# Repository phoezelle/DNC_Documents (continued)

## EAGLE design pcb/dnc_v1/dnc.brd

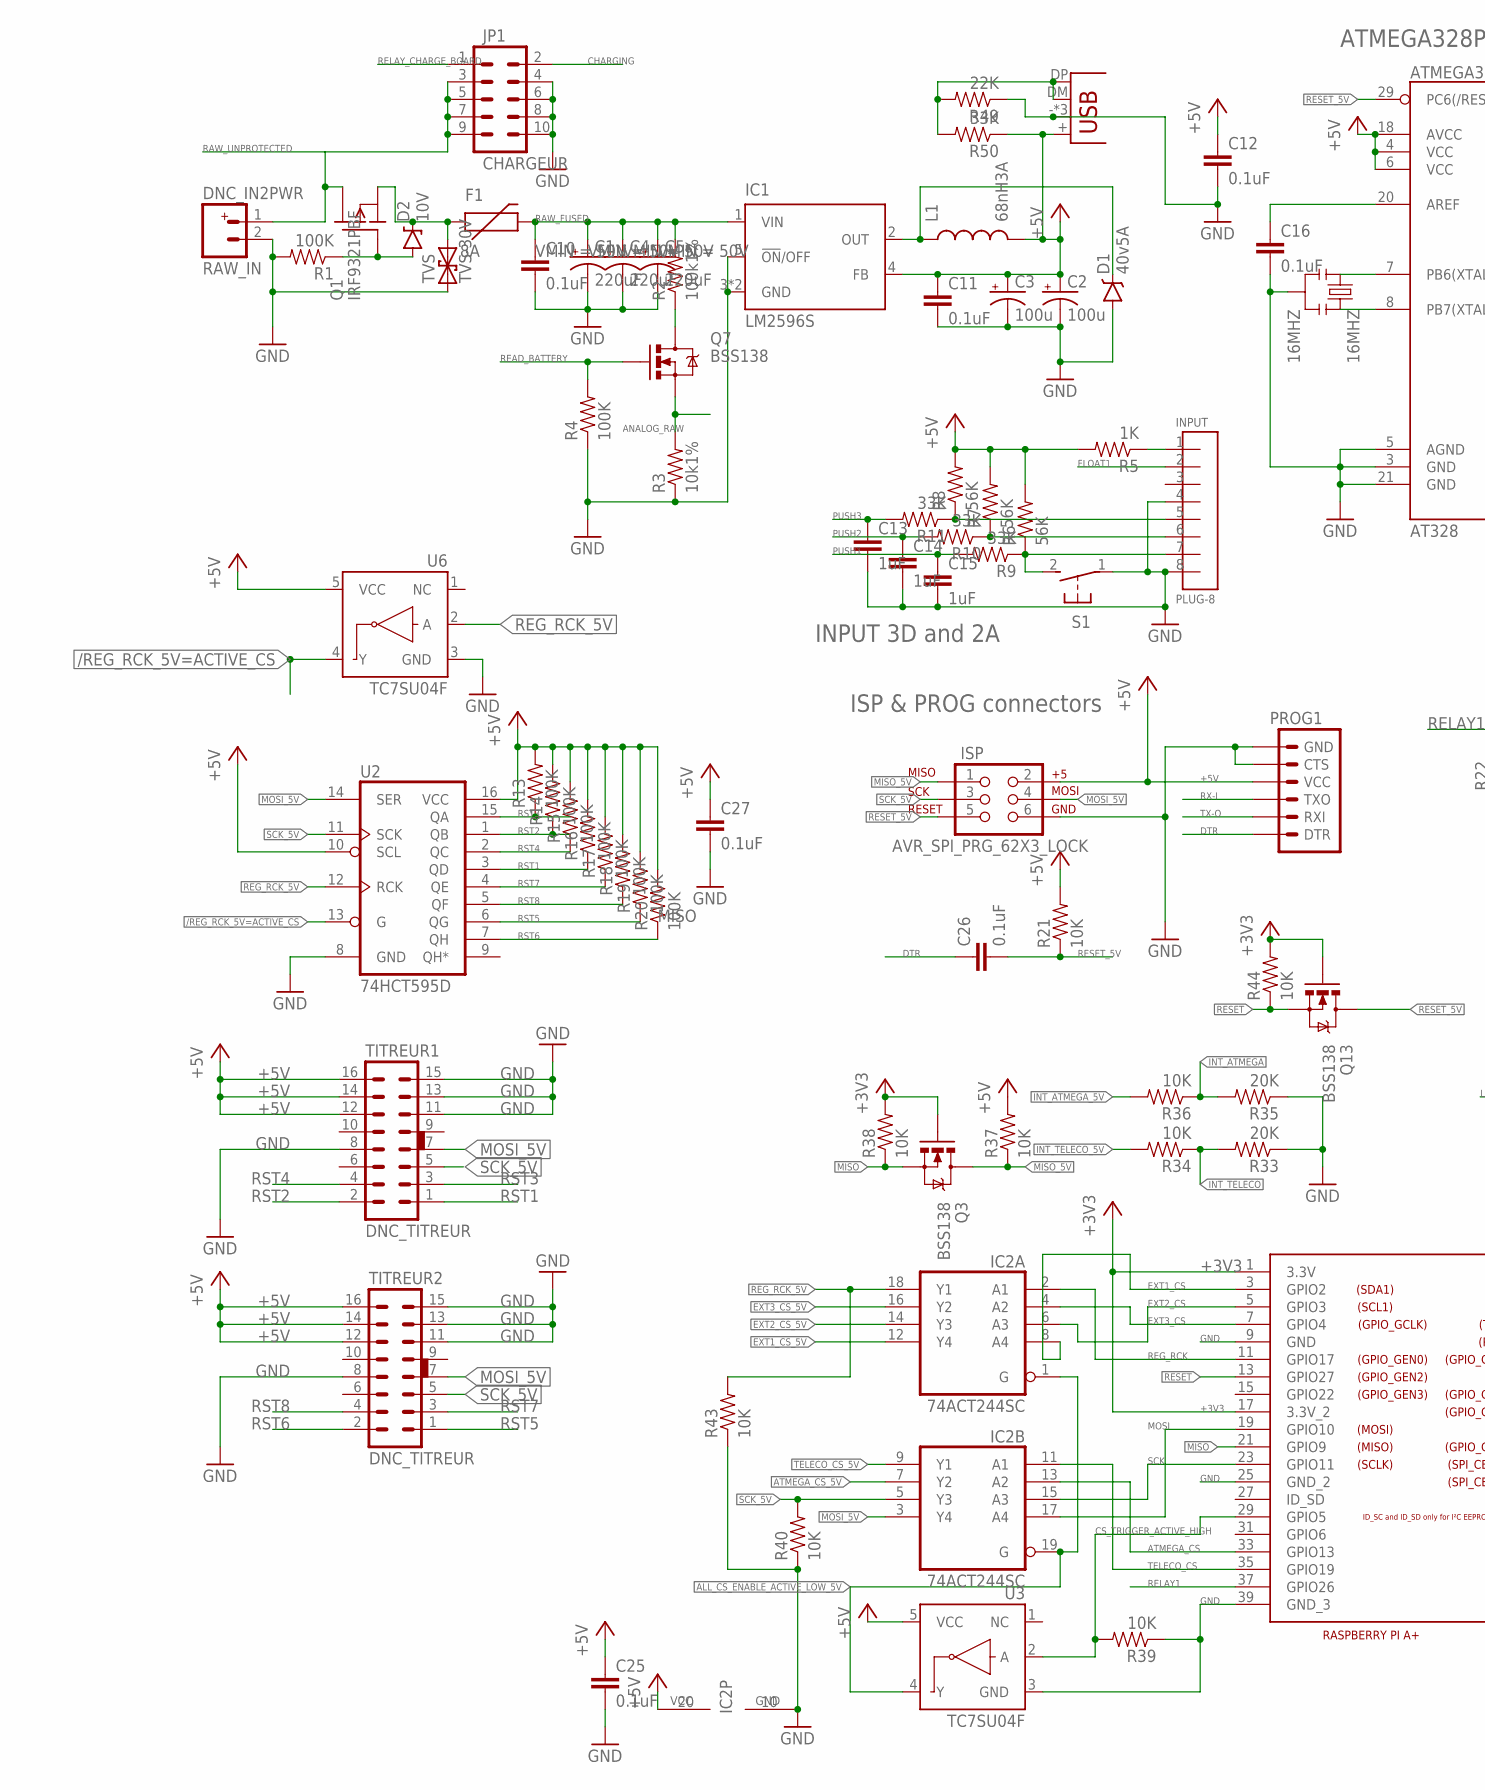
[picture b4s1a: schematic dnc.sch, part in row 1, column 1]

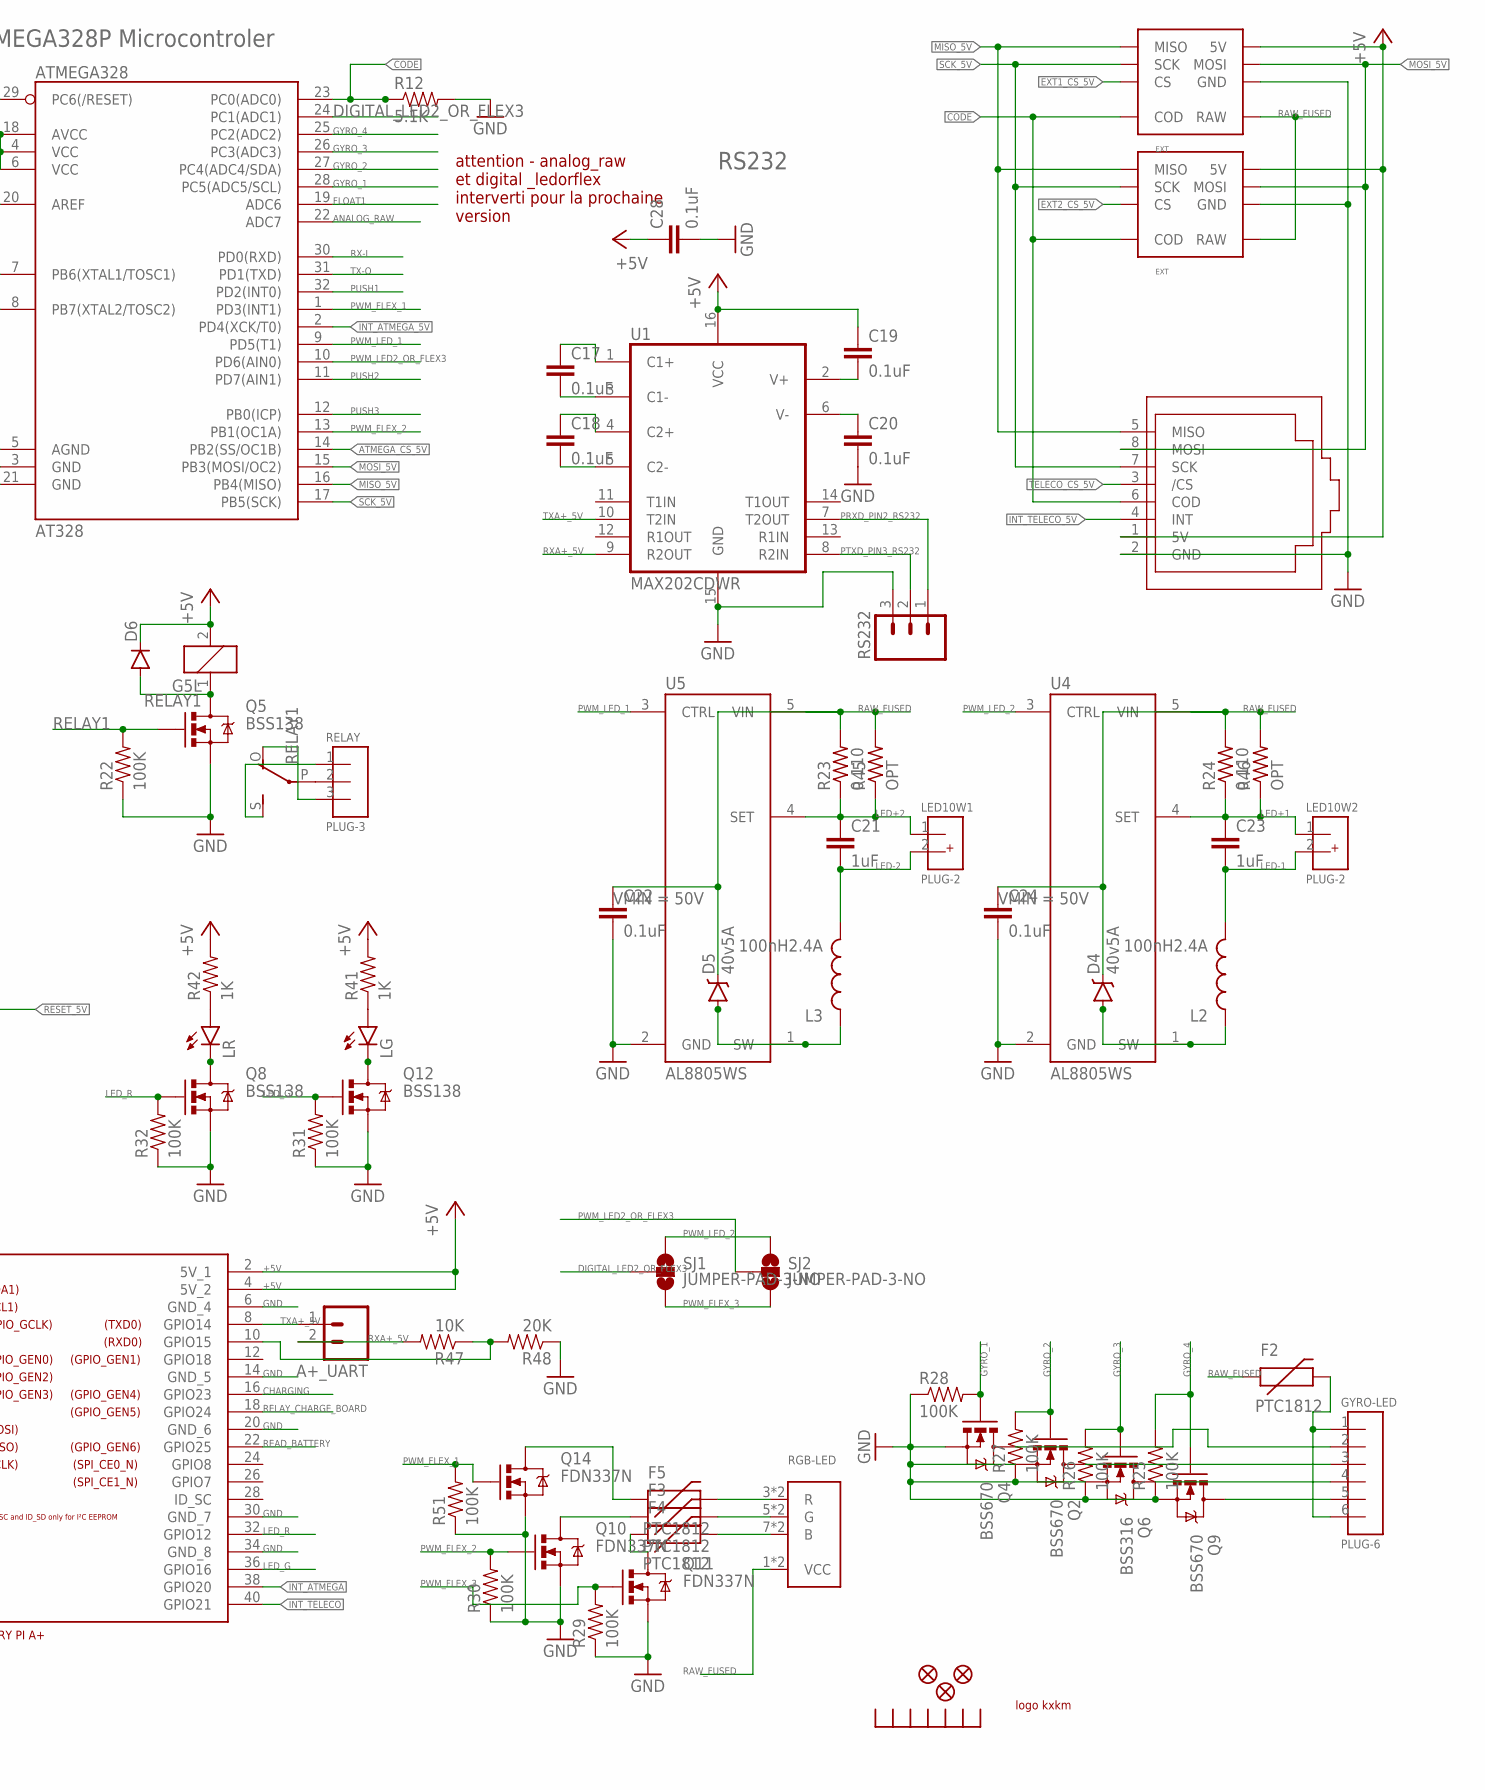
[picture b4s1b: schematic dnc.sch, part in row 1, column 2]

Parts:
16MHZ: 16MHZ; RESONATOR-SMD
A+_UART: M02LOCK_LONGPADS; 1X02_LOCK_LONGPADS
AT328: ATMEGA328; TQFP32-08
C1, C4, C5: 220uF; PANASONIC_E
C2, C3: 100u; PANASONIC_D
C10, C11, C12, C16, C17, C18, C19, C20, C22, C24, C25, C26, C27, C28: 0.1uF; C0603
C13, C14, C15, C21, C23: 1uF; C0603
D1, D4, D5: 40v5A; DO-221
D2: 10V; SOD-123
D6: DIODESMA-ALT; SMA-DIODE_ALT
EXT1, EXT2: EXT; EXTPINDNC
F1: 8A; PTC
F2, F3, F4, F5: PTC1812; PTC_1812
GYRO-LED: PLUG-6; PLUG_06
IC1: LM2596S; TO263-5
IC2: 74ACT244SC; SO20W
INPUT: PLUG-8; PLUG_08
ISP: AVR_SPI_PRG_62X3_LOCK; 2X3_LOCK
JP1: CHARGEUR; 2X5_LOCK
JP13, JP14, JP19: FIDUCIAL1X2.5; FIDUCIAL-1X2.5
L1: 68nH3A; CDRH125
L2, L3: 100nH2.4A; CDRH125
LED10W1, LED10W2: PLUG-2; PLUG_02
LG: LED1206; LED-1206
LR: LED1206; LED-1206
PROG1: ARDUINO_SERIAL_PROGRAMLOCK; 1X06_LOCK
Q1: IRF9321PBF; SO-8
Q2, Q4, Q9: BSS670; SOT23-3
Q3, Q5, Q7, Q8, Q12, Q13: BSS138; SOT23-3
Q6: BSS316; SOT23-3
Q10, Q11, Q14: FDN337N; SOT23-3
R1, R4, R13, R14, R15, R16, R17, R18, R19, R20, R22, R25, R26, R27, R28, R29, R30, R31, R32, R51: 100K; 0603-RES
R2: 100k1%; 0603-RES
R3: 10k1%; 0603-RES
R5, R41, R42: 1K; 0603-RES
R6, R7, R8: 56K; 0603-RES
R9, R10, R11, R50: 33K; 0603-RES
R12: 5.1K; 0603-RES
R21, R34, R36, R37, R38, R39, R40, R43, R44, R47: 10K; 0603-RES
R23, R24: 0.110; R0805
R33, R35, R48: 20K; 0603-RES
R45, R46: OPT; R0805
R49: 22K; 0603-RES
RAW_IN: DNC_IN2PWR; DNC_IN2_PWR
RELAY: PLUG-3; PLUG_03
RELAY1: G5L; G5LE
RGB-LED: RJ45-RGBLED; RJ45-TRAFO
RS232: M03LOCK; 1X03_LOCK
S1: 31-XX; B3F-31XX
SJ1, SJ2: JUMPER-PAD-3-NO; PAD-JUMPER-3-NO_YES_SILK_FULL_BOX_WIDE_SPACING
TITREUR1, TITREUR2: DNC_TITREUR
TVS: TVS-30V; SMA-DIODE
U1: MAX202CDWR; SO016
U2: 74HCT595D; SO16
U3, U6: TC7SU04F; SOT23-5
U4, U5: AL8805WS; SOT23-5
U$1: RADIATEUR; RADIATEUR_577102B00000G
U$2: LOGOSIZE2; KXKMLOGO2
U$4: RASPIA+
U$8: RJ45-EXTDNC; RJ45-TRAFO
X1: USB; USB_F_SATISTRONIC

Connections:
+3V3: Q3.1 (G), Q13.1 (G), R38.2, R44.2, U$4.1 (3.3V), U$4.17 (3.3V_2)
+5V: AT328.4 (VCC), AT328.6 (VCC), AT328.18 (AVCC), C2.+, C3.+, C11.1, C12.1, C19.1, C25.1, C27.1, C28.1, D6.C, EXT1.5V, EXT2.5V, IC1.4 (FB), IC2.20 (VCC), ISP.2, L1.2, PROG1.4 (VCC), R5.2, R6.2, R7.2, R8.2, R13.2, R14.2, R15.2, R16.2, R17.2, R18.2, R19.2, R20.2, R21.2, R37.2, R41.2, R42.2, R50.1, RELAY1.2, TITREUR1.12, TITREUR1.14, TITREUR1.16, TITREUR2.12, TITREUR2.14, TITREUR2.16, U1.16 (VCC), U2.10 (SCL), U2.16 (VCC), U3.5 (VCC), U6.5 (VCC), U$4.2 (5V_1), U$4.4 (5V_2), U$8.1 (5V), X1.+ (V+)
/REG_RCK_5V=ACTIVE_CS: U2.13 (G), U6.4 (Y)
ALL_CS_ENABLE_ACTIVE_LOW_5V: IC2.1 (G), IC2.19 (G), U3.4 (Y)
ANALOG_RAW: AT328.22 (ADC7), Q7.2 (S), R3.2
AREF: AT328.20 (AREF), C16.1
ATMEGA_CS: IC2.13 (A2), U$4.33 (GPIO13)
ATMEGA_CS_5V: AT328.14 (PB2(SS/OC1B)), IC2.7 (Y2)
BB: F4.2, RGB-LED.7 (B), RGB-LED.8 (B)
CHARGING: JP1.2, U$4.16 (GPIO23)
CODE: AT328.23 (PC0(ADC0)), EXT1.RETOURANALOG (COD), EXT2.RETOURANALOG (COD), R12.1, U$8.6 (COD)
CS_TRIGGER_ACTIVE_HIGH: R39.2, U3.2 (A), U$4.29 (GPIO5)
DIGITAL_LED2_OR_FLEX3: AT328.24 (PC1(ADC1)), SJ1.2
DTR: C26.1, PROG1.1 (DTR)
EXT1_CS: IC2.8 (A4), U$4.3 (GPIO2)
EXT1_CS_5V: EXT1./CS (CS), IC2.12 (Y4)
EXT2_CS: IC2.6 (A3), U$4.5 (GPIO3)
EXT2_CS_5V: EXT2./CS (CS), IC2.14 (Y3)
EXT3_CS: IC2.4 (A2), U$4.7 (GPIO4)
EXT3_CS_5V: IC2.16 (Y2)
FLOAT1: AT328.19 (ADC6), INPUT.2
GG: F3.2, RGB-LED.5 (G), RGB-LED.6 (G)
GND: 16MHZ.2, AT328.3 (GND), AT328.5 (AGND), AT328.21 (GND), C1.-, C2.-, C3.-, C4.-, C5.-, C10.2, C11.2, C12.2, C13.2, C14.2, C15.2, C16.2, C20.2, C22.2, C24.2, C25.2, C27.2, C28.2, D1.A, EXT1.1_GND (GND), EXT1.GND2 (GND), EXT2.1_GND (GND), EXT2.GND2 (GND), IC1.3 (GND), IC1.5 (!ON!/OFF), IC1.THERMAL (GND), IC2.10 (GND), INPUT.4, INPUT.8, ISP.6, JP1.4, JP1.6, JP1.8, JP1.10, PROG1.5 (CTS), PROG1.6 (GND), Q2.2 (S), Q4.2 (S), Q5.2 (S), Q6.2 (S), Q8.2 (S), Q9.2 (S), Q10.2 (S), Q11.2 (S), Q12.2 (S), Q14.2 (S), R1.2, R3.1, R4.1, R12.2, R22.1, R25.1, R26.1, R27.1, R28.1, R29.1, R30.1, R31.1, R32.1, R33.1, R35.1, R39.1, R40.1, R43.1, R48.1, R49.1, R51.1, RAW_IN.2 (-), RS232.3, S1.1, TITREUR1.8, TITREUR1.11, TITREUR1.13, TITREUR1.15, TITREUR2.8, TITREUR2.11, TITREUR2.13, TITREUR2.15, TVS.A (1), U1.15 (GND), U2.8 (GND), U3.3 (GND), U4.2 (GND), U5.2 (GND), U6.3 (GND), U$4.6 (GND_4), U$4.9 (GND), U$4.14 (GND_5), U$4.20 (GND_6), U$4.25 (GND_2), U$4.30 (GND_7), U$4.34 (GND_8), U$4.39 (GND_3), U$8.2 (GND), X1.- (GND), X1.S1 (GND), X1.S2 (GND)
GYRO_1: AT328.28 (PC5(ADC5/SCL)), Q4.1 (G), R28.2
GYRO_2: AT328.27 (PC4(ADC4/SDA)), Q2.1 (G), R27.2
GYRO_3: AT328.26 (PC3(ADC3)), Q6.1 (G), R26.2
GYRO_4: AT328.25 (PC2(ADC2)), Q9.1 (G), R25.2
INT_ATMEGA: R35.2, R36.1, U$4.38 (GPIO20)
INT_ATMEGA_5V: AT328.2 (PD4(XCK/T0)), R36.2
INT_TELECO: R33.2, R34.1, U$4.40 (GPIO21)
INT_TELECO_5V: R34.2, U$8.4 (INT)
LED+1: C23.1, LED10W2.1, R24.1, R46.1, U4.4 (SET)
LED+2: C21.1, LED10W1.1, R23.1, R45.1, U5.4 (SET)
LED-1: C23.2, L2.2, LED10W2.2
LED-2: C21.2, L3.2, LED10W1.2
LEDR: LR.C, Q8.3 (D)
LED_G: Q12.1 (G), R31.2, U$4.36 (GPIO16)
LED_R: Q8.1 (G), R32.2, U$4.32 (GPIO12)
LG: LG.C, Q12.3 (D)
MISO: Q3.2 (S), R38.1, U$4.21 (GPIO9)
MISO_5V: AT328.16 (PB4(MISO)), EXT1.MISO, EXT2.MISO, ISP.1, Q3.3 (D), R37.1, U$8.5 (MISO)
MOSI: IC2.17 (A4), U$4.19 (GPIO10)
MOSI_5V: AT328.15 (PB3(MOSI/OC2)), EXT1.MOSI, EXT2.MOSI, IC2.3 (Y4), ISP.4, TITREUR1.7, TITREUR2.7, U2.14 (SER), U$8.8 (MOSI)
unnamed: D1.C, IC1.2 (OUT), L1.1
unnamed: Q7.3 (D), R2.1
unnamed: F2.2, GYRO-LED.1, GYRO-LED.6
unnamed: D4.A, L2.1, U4.1 (SW)
unnamed: D5.A, L3.1, U5.1 (SW)
unnamed: RELAY.2, RELAY1.P
unnamed: GYRO-LED.2, Q4.3 (D)
unnamed: GYRO-LED.3, Q2.3 (D)
unnamed: GYRO-LED.4, Q6.3 (D)
unnamed: GYRO-LED.5, Q9.3 (D)
unnamed: D6.A, Q5.3 (D), RELAY1.1
unnamed: F4.1, Q11.3 (D)
unnamed: LG.A, R41.1
unnamed: F3.1, Q10.3 (D)
unnamed: LR.A, R42.1
unnamed: C19.2, U1.2 (V+)
unnamed: INPUT.1, R5.1
unnamed: R49.2, R50.2, X1.DM (D-), X1.DP (D+)
unnamed: F5.1, Q14.3 (D)
unnamed: C20.1, U1.6 (V-)
unnamed: 16MHZ.1, AT328.7 (PB6(XTAL1/TOSC1))
unnamed: 16MHZ.3, AT328.8 (PB7(XTAL2/TOSC2))
unnamed: C18.2, U1.5 (C2-)
unnamed: C18.1, U1.4 (C2+)
unnamed: C17.2, U1.3 (C1-)
unnamed: C17.1, U1.1 (C1+)
PROTECT_GATE: D2.A, Q1.4 (G), R1.1
PRXD_PIN2_RS232: RS232.1, U1.7 (T2OUT)
PTXD_PIN3_RS232: RS232.2, U1.8 (R2IN)
PUSH1: AT328.32 (PD2(INT0)), C15.1, R9.2
PUSH2: AT328.11 (PD7(AIN1)), C14.1, R10.2
PUSH3: AT328.12 (PB0(ICP)), C13.1, R11.2
PWM_FLEX_1: AT328.1 (PD3(INT1)), Q14.1 (G), R51.2
PWM_FLEX_2: AT328.13 (PB1(OC1A)), Q10.1 (G), R30.2
PWM_FLEX_3: Q11.1 (G), R29.2, SJ1.3, SJ2.3
PWM_LED2_OR_FLEX3: AT328.10 (PD6(AIN0)), SJ2.2
PWM_LED_1: AT328.9 (PD5(T1)), U5.3 (CTRL)
PWM_LED_2: SJ1.1, SJ2.1, U4.3 (CTRL)
RAW_FUSED: C1.+, C4.+, C5.+, C10.1, C22.1, C24.1, D4.C, D5.C, EXT1.RAW, EXT1.RAW2 (RAW), EXT2.RAW, EXT2.RAW2 (RAW), F1.P$2 (2), F2.1, IC1.1 (VIN), R2.2, R23.2, R24.2, R45.2, R46.2, RGB-LED.1 (VCC), RGB-LED.2 (VCC), U4.5 (VIN), U5.5 (VIN)
RAW_POL_PROTECTED: D2.C, F1.P$1MOV (1), Q1.1 (S), Q1.2 (S), Q1.3 (S), TVS.C (2)
RAW_UNPROTECTED: JP1.3, JP1.5, JP1.7, JP1.9, Q1.5 (D), Q1.6 (D), Q1.7 (D), Q1.8 (D), RAW_IN.1 (+)
READ_BATTERY: Q7.1 (G), R4.2, U$4.22 (GPIO25)
REG_RCK: IC2.2 (A1), U$4.11 (GPIO17)
REG_RCK_5V: IC2.18 (Y1), R43.2, U2.12 (RCK), U6.2 (A)
RELAY1: Q5.1 (G), R22.2, U$4.37 (GPIO26)
RELAY_CHARGE_BOARD: JP1.1, U$4.18 (GPIO24)
RESET: Q13.2 (S), R44.1, U$4.13 (GPIO27)
RESET_5V: AT328.29 (PC6(/RESET)), C26.2, ISP.5, Q13.3 (D), R21.1
RNC: RELAY.3, RELAY1.O
RNO: RELAY.1, RELAY1.S
RR: F5.2, RGB-LED.3 (R), RGB-LED.4 (R)
RST1: R16.1, TITREUR1.1, U2.3 (QD)
RST2: R14.1, TITREUR1.2, U2.1 (QB)
RST3: R13.1, TITREUR1.3, U2.15 (QA)
RST4: R15.1, TITREUR1.4, U2.2 (QC)
RST5: R19.1, TITREUR2.1, U2.6 (QG)
RST6: R20.1, TITREUR2.2, U2.7 (QH)
RST7: R17.1, TITREUR2.3, U2.4 (QE)
RST8: R18.1, TITREUR2.4, U2.5 (QF)
RX-I: AT328.30 (PD0(RXD)), PROG1.3 (TXO)
RXA+: R47.1, R48.2, U$4.10 (GPIO15)
RXA+_5V: A+_UART.2, R47.2, U1.9 (R2OUT)
S1: INPUT.7, R6.1, R9.1, S1.2 (S)
S2: INPUT.6, R7.1, R10.1
S3: INPUT.5, R8.1, R11.1
SCK: IC2.15 (A3), U$4.23 (GPIO11)
SCK_5V: AT328.17 (PB5(SCK)), EXT1.SCK, EXT2.SCK, IC2.5 (Y3), ISP.3, R40.2, TITREUR1.5, TITREUR2.5, U2.11 (SCK), U$8.7 (SCK)
TELECO_CS: IC2.11 (A1), U$4.35 (GPIO19)
TELECO_CS_5V: IC2.9 (Y1), U$8.3 (/CS)
TX-O: AT328.31 (PD1(TXD)), PROG1.2 (RXI)
TXA+_5V: A+_UART.1, U1.10 (T2IN), U$4.8 (GPIO14)

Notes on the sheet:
ATMEGA328P Microcontroler
ISP & PROG connectors
INPUT 3D and 2A
RS232
attention - analog_raw et digital _ledorflex interverti pour la prochaine version

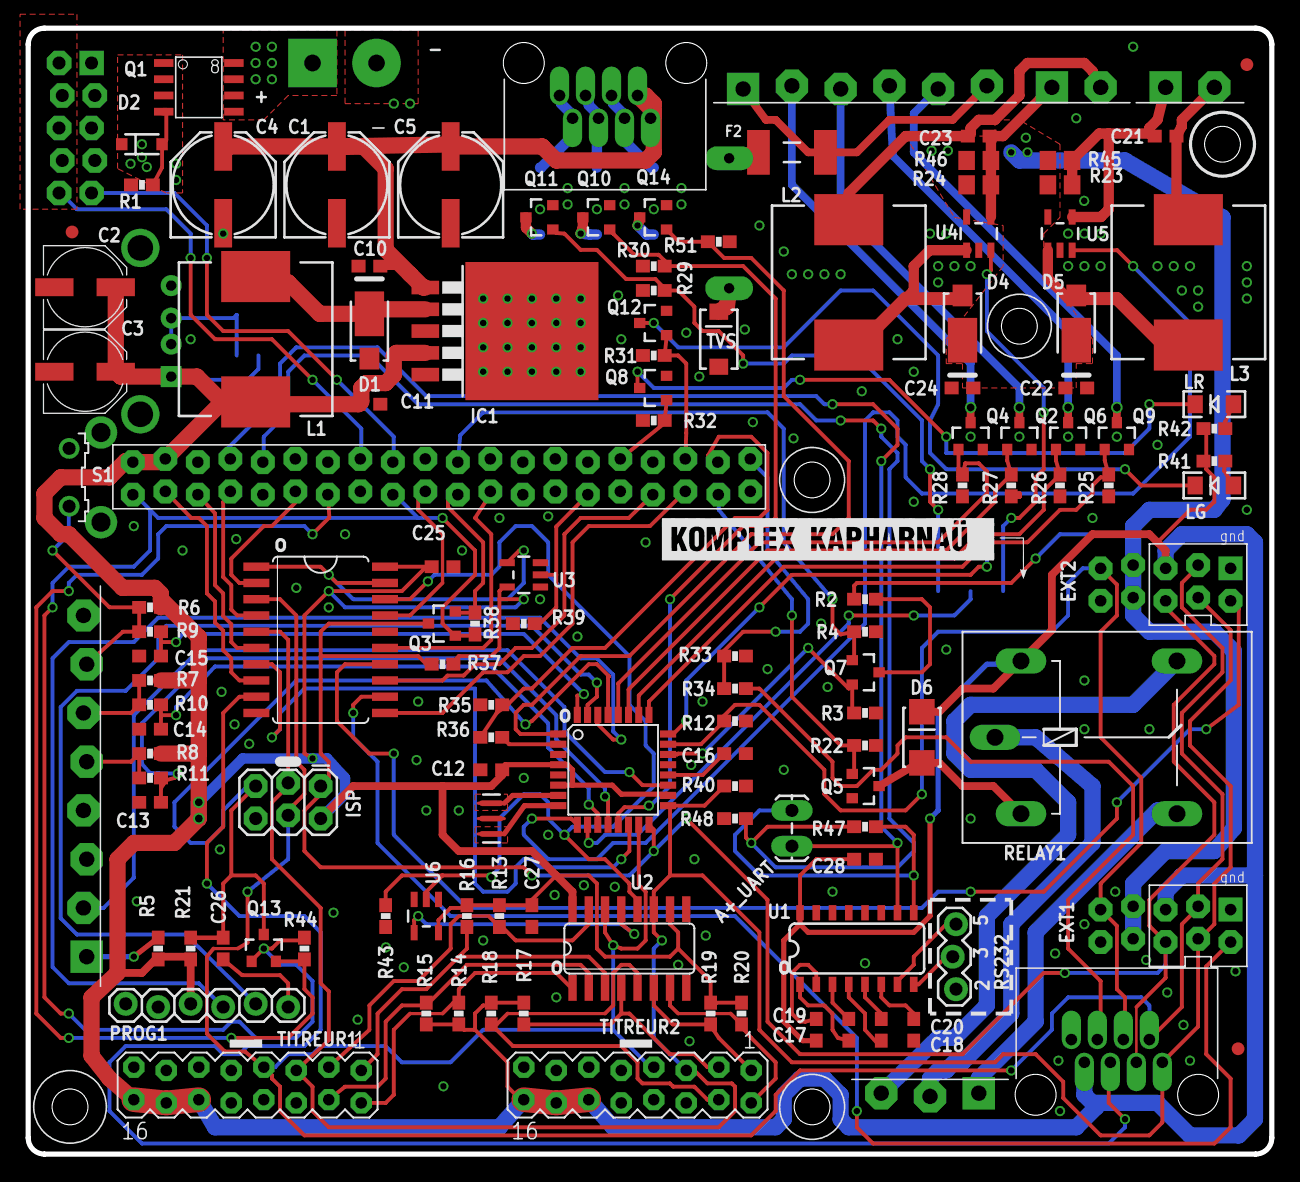
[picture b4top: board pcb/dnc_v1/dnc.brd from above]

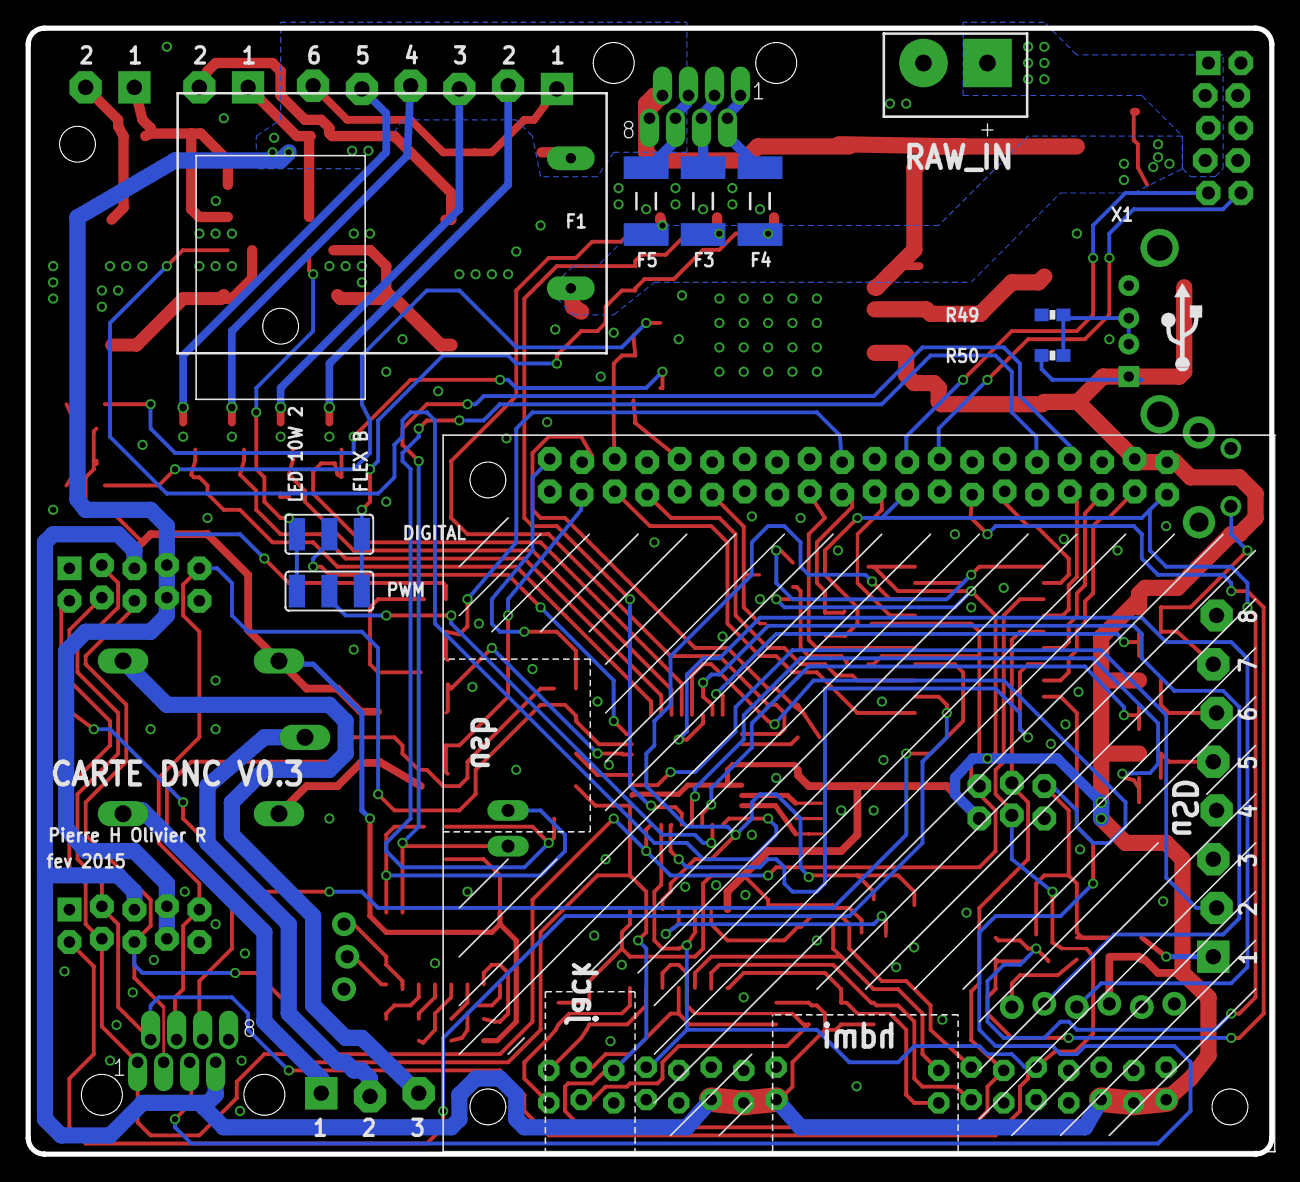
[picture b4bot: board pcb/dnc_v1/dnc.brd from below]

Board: 2 copper layers, 97.2 x 88.0 mm, 143 parts (11 on the bottom side), 113 nets.

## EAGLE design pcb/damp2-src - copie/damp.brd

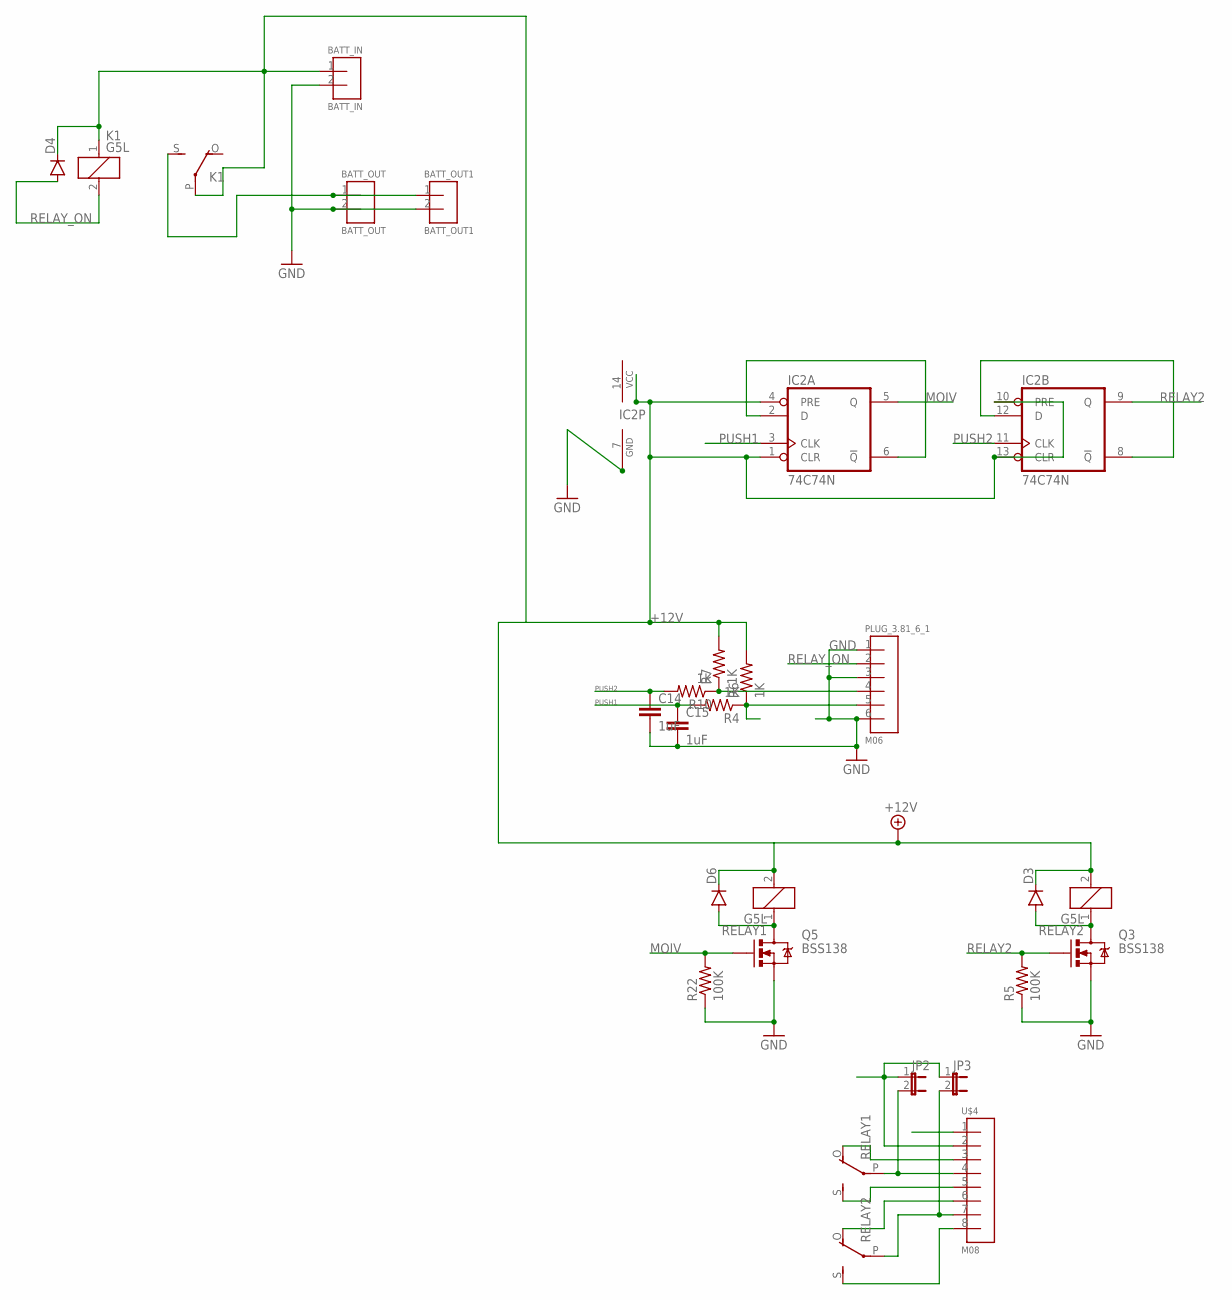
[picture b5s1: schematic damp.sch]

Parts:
BATT_IN: BATT_IN; PLUG_02
BATT_OUT: BATT_OUT; PLUG_02
BATT_OUT1: BATT_OUT1; PLUG_02
C14, C15: 1uF; C0603
D3, D4, D6: DIODESMA-ALT; SMA-DIODE_ALT
IC2: 74C74N; DIL14
JP2, JP3: JP1E; JP1
K1: G5L; G5LE
PLUG_3.81_6_1: M06; PLUG_06
Q3, Q5: BSS138; SOT23-3
R4, R6, R7, R10: 1K; 0603-RES
R5, R22: 100K; 0603-RES
RELAY1, RELAY2: G5L; G5LE
U$4: M08; PLUG_08

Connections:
+12V: BATT_IN.1, D3.C, D4.C, D6.C, IC2.1 (CLR), IC2.4 (PRE), IC2.10 (PRE), IC2.13 (CLR), K1.1, K1.P, R6.2, R7.2, RELAY1.2, RELAY2.2
AUDIO_OUT1: JP2.1, JP3.1, U$4.2
AUDIO_OUT2: U$4.1
GND: BATT_IN.2, BATT_OUT.2, BATT_OUT1.2, C14.2, C15.2, IC2.7 (GND), PLUG_3.81_6_1.1, PLUG_3.81_6_1.3, PLUG_3.81_6_1.6, Q3.2 (S), Q5.2 (S), R5.1, R22.1
MOIV: IC2.5 (Q), Q5.1 (G), R22.2
unnamed: JP2.2, RELAY1.P, U$4.4
unnamed: RELAY1.O, U$4.3
unnamed: RELAY1.S, U$4.5
unnamed: RELAY2.O, U$4.6
unnamed: RELAY2.S, U$4.8
unnamed: D6.A, Q5.3 (D), RELAY1.1
unnamed: PLUG_3.81_6_1.4, R7.1, R10.1
unnamed: JP3.2, RELAY2.P, U$4.7
unnamed: PLUG_3.81_6_1.5, R4.1, R6.1
unnamed: D3.A, Q3.3 (D), RELAY2.1
unnamed: IC2.2 (D), IC2.6 (!Q)
unnamed: IC2.8 (!Q), IC2.12 (D)
unnamed: BATT_OUT.1, BATT_OUT1.1, K1.S
PUSH1: C15.1, IC2.3 (CLK), R4.2
PUSH2: C14.1, IC2.11 (CLK), R10.2
RELAY2: IC2.9 (Q), Q3.1 (G), R5.2
RELAY_ON: D4.A, K1.2, PLUG_3.81_6_1.2
VCC: IC2.14 (VCC)

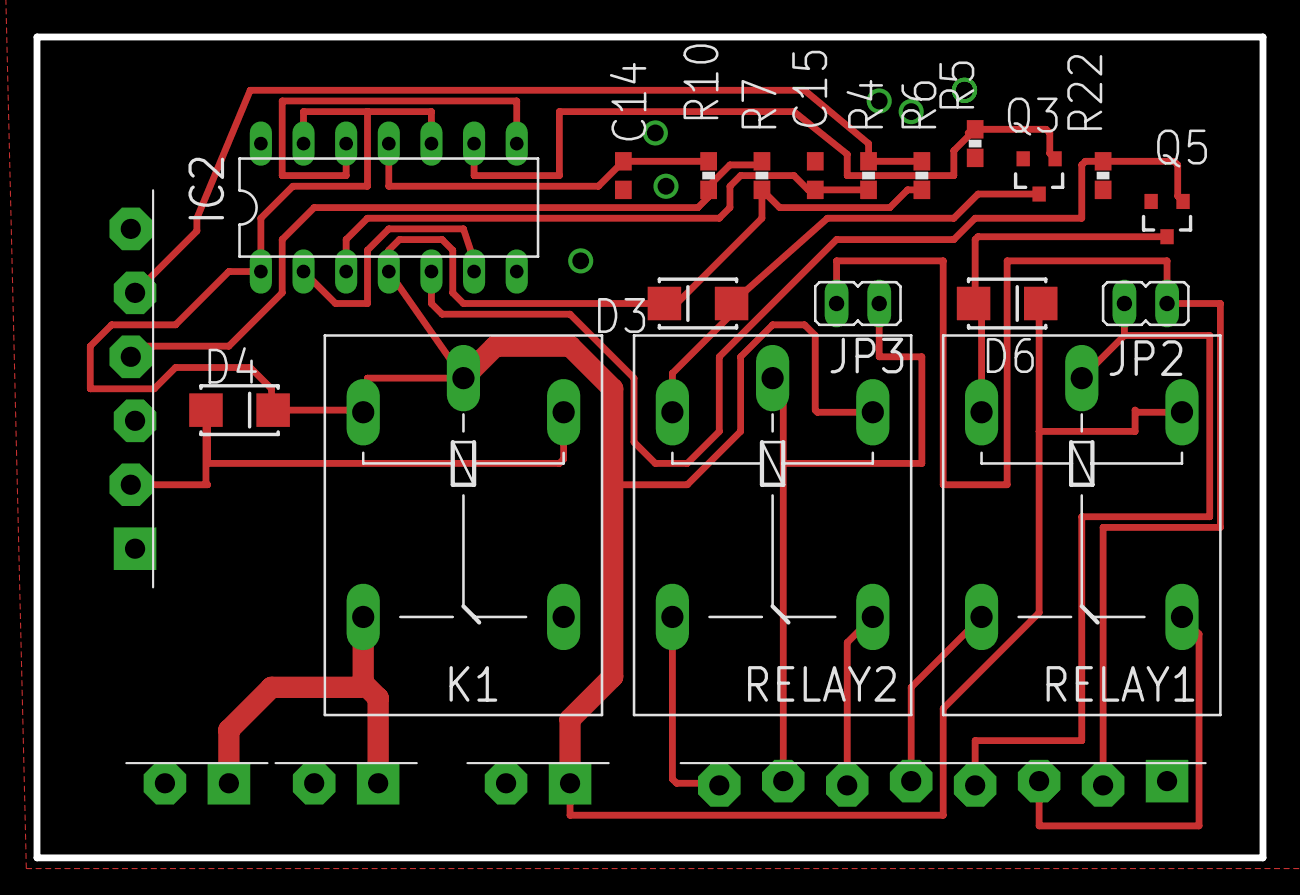
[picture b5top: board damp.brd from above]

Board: 2 copper layers, 73.0 x 48.9 mm, 24 parts (0 on the bottom side), 21 nets.

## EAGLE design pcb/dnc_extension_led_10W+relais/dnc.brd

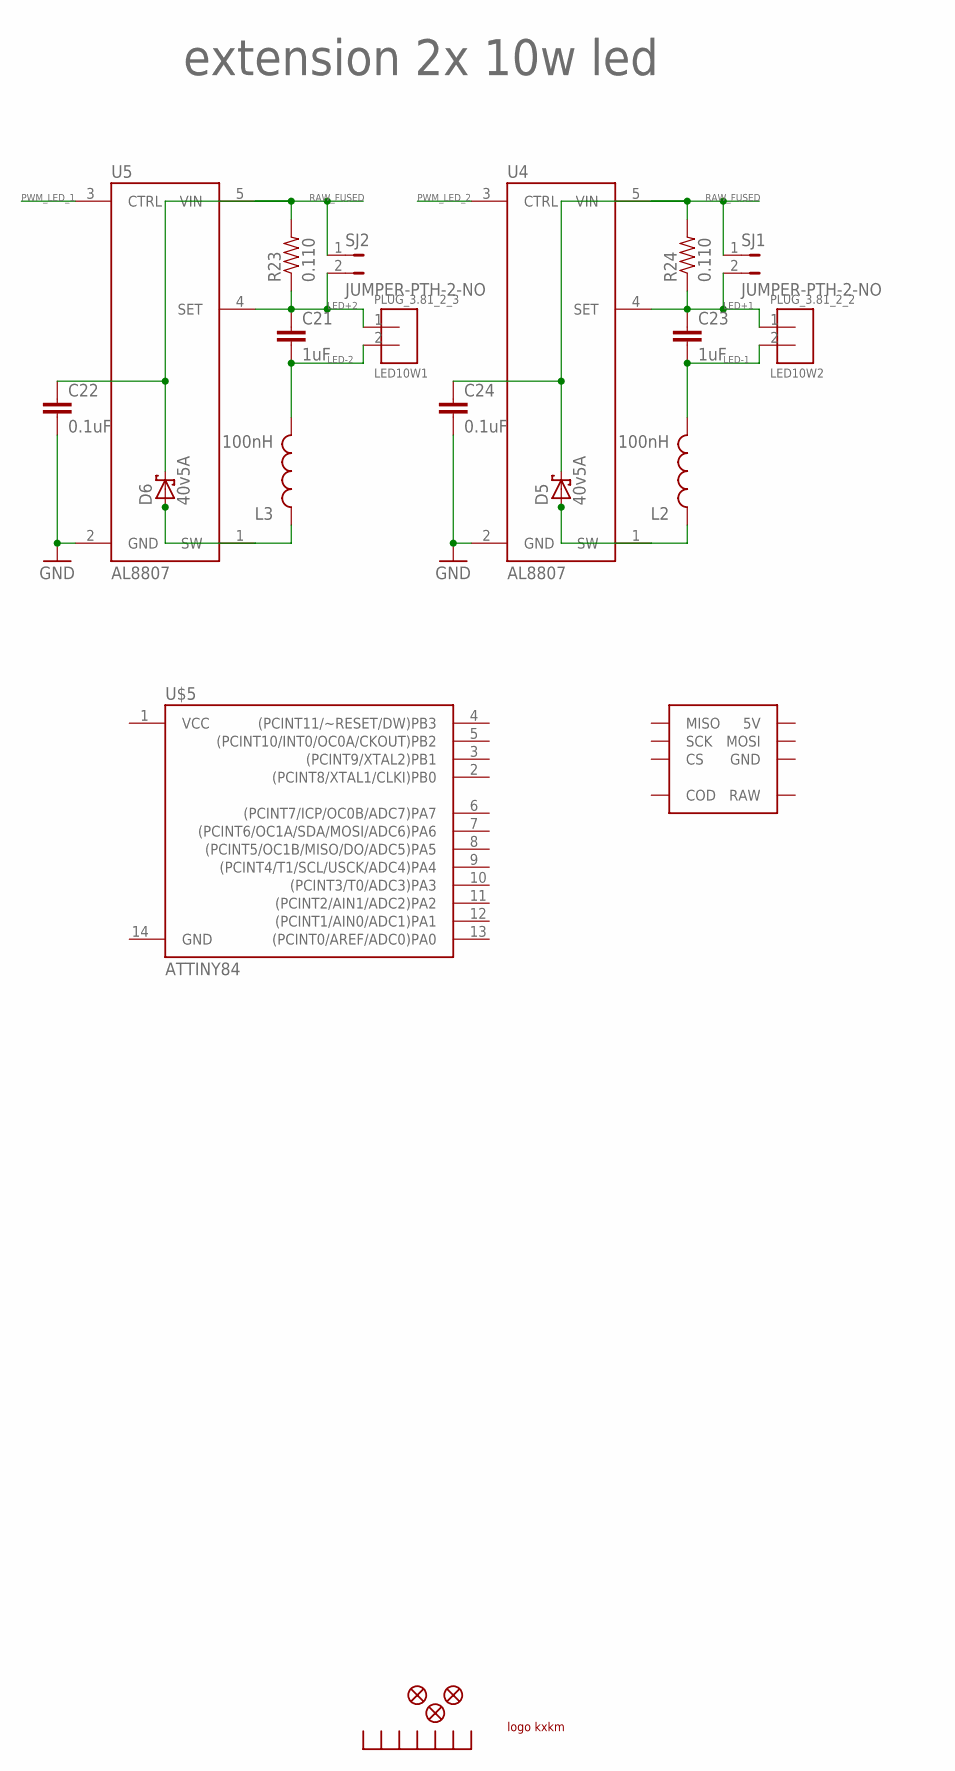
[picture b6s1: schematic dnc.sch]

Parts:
C21, C23: 1uF; C0603
C22, C24: 0.1uF; C0603
D5, D6: 40v5A; SMC
JP13, JP14, JP19: FIDUCIAL1X2.5; FIDUCIAL-1X2.5
L2, L3: 100nH; CDRH125
PLUG_3.81_2_2: LED10W2; PLUG_02
PLUG_3.81_2_3: LED10W1; PLUG_02
R23, R24: 0.110; 0603-RES
SJ1, SJ2: JUMPER-PTH-2-NO; PTH-JUMPER-2-NO_NO_SILK
U4, U5: AL8807; SOT23-5
U$1: RADIATEUR; RADIATEUR_577102B00000G
U$2: LOGO; KXKMLOGO
U$5: ATTINY84; SO14
U$6: EXT-DNCCARTE_EXTENSION; 2X5_RIGHTANGLEDNC

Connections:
GND: C22.2, C24.2, U4.2 (GND), U5.2 (GND)
LED+1: C23.1, PLUG_3.81_2_2.1, R24.1, SJ1.2, U4.4 (SET)
LED+2: C21.1, PLUG_3.81_2_3.1, R23.1, SJ2.2, U5.4 (SET)
LED-1: C23.2, L2.2, PLUG_3.81_2_2.2
LED-2: C21.2, L3.2, PLUG_3.81_2_3.2
unnamed: D5.A, L2.1, U4.1 (SW)
unnamed: D6.A, L3.1, U5.1 (SW)
PWM_LED_1: U5.3 (CTRL)
PWM_LED_2: U4.3 (CTRL)
RAW_FUSED: C22.1, C24.1, D5.C, D6.C, R23.2, R24.2, SJ1.1, SJ2.1, U4.5 (VIN), U5.5 (VIN)

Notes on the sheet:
extension 2x 10w led

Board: 2 copper layers, 23 parts (0 on the bottom side), 8 nets, no tracks yet.

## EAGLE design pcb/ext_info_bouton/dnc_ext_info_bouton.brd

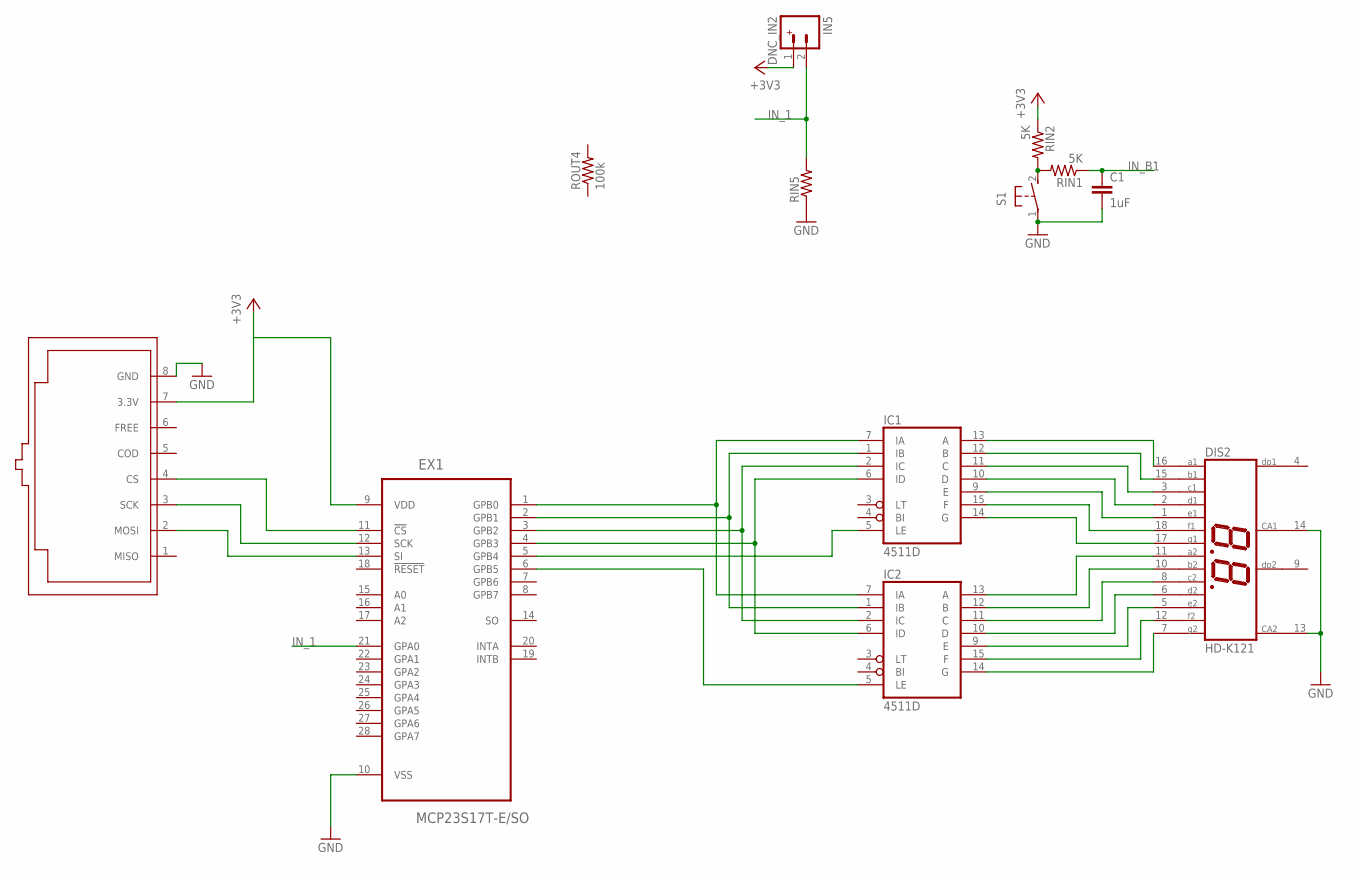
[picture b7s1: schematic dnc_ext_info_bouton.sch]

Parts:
C1: 1uF; 0603-CAP
DIS2: HD-K121; HDSP-R
EX1: MCP23S17T-E/SO; SOIC127P1030X265-28N
IC1, IC2: 4511D; SO16
IN5: DNC_IN2
RIN1, RIN2: 5K; 0603-RES
RIN5: RESISTOR0603-RES; 0603-RES
ROUT4: 100k; 0603-RES
S1: 31-XX; B3F-31XX
U$6: RJ45-EXTDNC; RJ45-TRAFO

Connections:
+3V3: EX1.9 (VDD), IN5.1, RIN2.1, U$6.7 (3.3V)
GND: C1.2, DIS2.13 (CA2), DIS2.14 (CA1), EX1.10 (VSS), RIN5.1, S1.1, U$6.8 (GND)
IN_1: EX1.21 (GPA0), IN5.2, RIN5.2
IN_B1: C1.1, RIN1.1
unnamed: RIN1.2, RIN2.2, S1.2 (S)
unnamed: EX1.11 (!CS), U$6.4 (CS)
unnamed: EX1.12 (SCK), U$6.3 (SCK)
unnamed: EX1.13 (SI), U$6.2 (MOSI)
unnamed: EX1.1 (GPB0), IC1.7 (IA), IC2.7 (IA)
unnamed: EX1.2 (GPB1), IC1.1 (IB), IC2.1 (IB)
unnamed: EX1.3 (GPB2), IC1.2 (IC), IC2.2 (IC)
unnamed: EX1.4 (GPB3), IC1.6 (ID), IC2.6 (ID)
unnamed: EX1.5 (GPB4), IC1.5 (LE)
unnamed: EX1.6 (GPB5), IC2.5 (LE)
unnamed: DIS2.16 (A1), IC1.13 (A)
unnamed: DIS2.15 (B1), IC1.12 (B)
unnamed: DIS2.3 (C1), IC1.11 (C)
unnamed: DIS2.2 (D1), IC1.10 (D)
unnamed: DIS2.1 (E1), IC1.9 (E)
unnamed: DIS2.18 (F1), IC1.15 (F)
unnamed: DIS2.17 (G1), IC1.14 (G)
unnamed: DIS2.11 (A2), IC2.13 (A)
unnamed: DIS2.10 (B2), IC2.12 (B)
unnamed: DIS2.8 (C2), IC2.11 (C)
unnamed: DIS2.6 (D2), IC2.10 (D)
unnamed: DIS2.5 (E2), IC2.9 (E)
unnamed: DIS2.12 (F2), IC2.15 (F)
unnamed: DIS2.7 (G2), IC2.14 (G)
VDD: IC1.16 (VDD), IC2.16 (VDD)
VSS: IC1.8 (VSS), IC2.8 (VSS)

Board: 2 copper layers, 12 parts (0 on the bottom side), 30 nets, no tracks yet.
